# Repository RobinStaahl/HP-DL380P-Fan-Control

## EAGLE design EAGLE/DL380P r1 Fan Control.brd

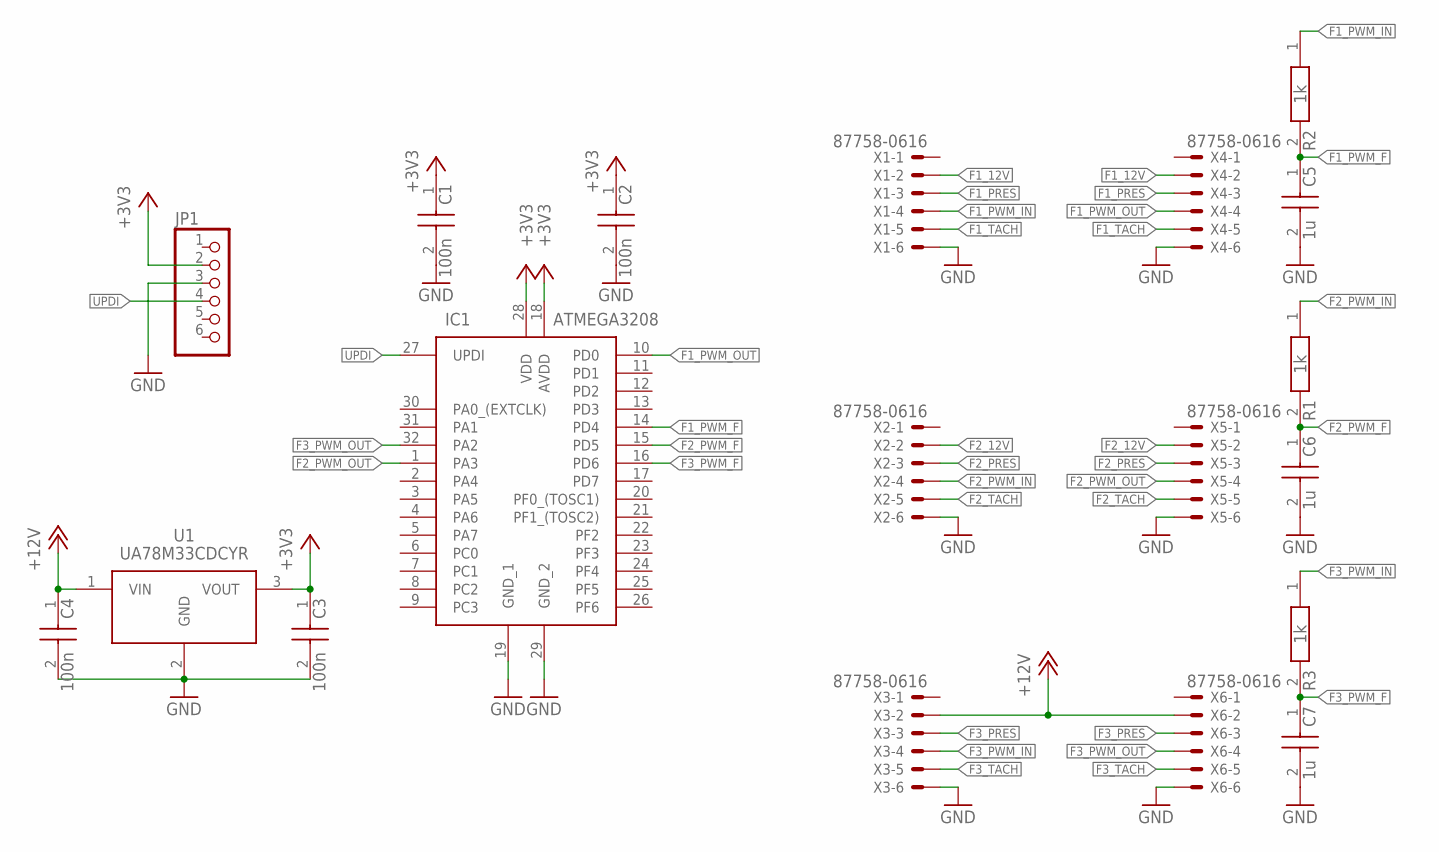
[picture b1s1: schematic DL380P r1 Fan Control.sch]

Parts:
C1, C2, C3, C4: 100n; CAPC1608X90N
C5, C6, C7: 1u; CAPC1608X90N
IC1: ATMEGA3208; QFP80P900X900X120-32N
JP1: PINHD-1X6LOCK; 1X06-BIGLOCK
R1, R2, R3: 1k; RESC1608X55N
U1: UA78M33CDCYR; SOT230P700X180-4N
X1, X2, X3, X4, X5, X6: 87758-0616

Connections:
+3V3: C1.1, C2.1, C3.1, IC1.18 (AVDD), IC1.28 (VDD), JP1.2, U1.3 (VOUT)
+12V: C4.1, U1.1 (VIN), X3.2, X6.2
F1_12V: X1.2, X4.2
F1_PRES: X1.3, X4.3
F1_PWM_F: C5.1, IC1.14 (PD4), R2.2
F1_PWM_IN: R2.1, X1.4
F1_PWM_OUT: IC1.10 (PD0), X4.4
F1_TACH: X1.5, X4.5
F2_12V: X2.2, X5.2
F2_PRES: X2.3, X5.3
F2_PWM_F: C6.1, IC1.15 (PD5), R1.2
F2_PWM_IN: R1.1, X2.4
F2_PWM_OUT: IC1.1 (PA3), X5.4
F2_TACH: X2.5, X5.5
F3_PRES: X3.3, X6.3
F3_PWM_F: C7.1, IC1.16 (PD6), R3.2
F3_PWM_IN: R3.1, X3.4
F3_PWM_OUT: IC1.32 (PA2), X6.4
F3_TACH: X3.5, X6.5
GND: C1.2, C2.2, C3.2, C4.2, C5.2, C6.2, C7.2, IC1.19 (GND_1), IC1.29 (GND_2), JP1.3, U1.2 (GND), U1.4 (GND_1), X1.6, X2.6, X3.6, X4.6, X5.6, X6.6
UPDI: IC1.27 (UPDI), JP1.4

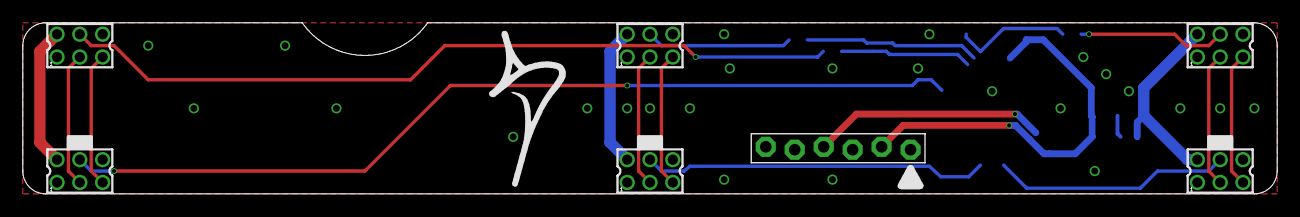
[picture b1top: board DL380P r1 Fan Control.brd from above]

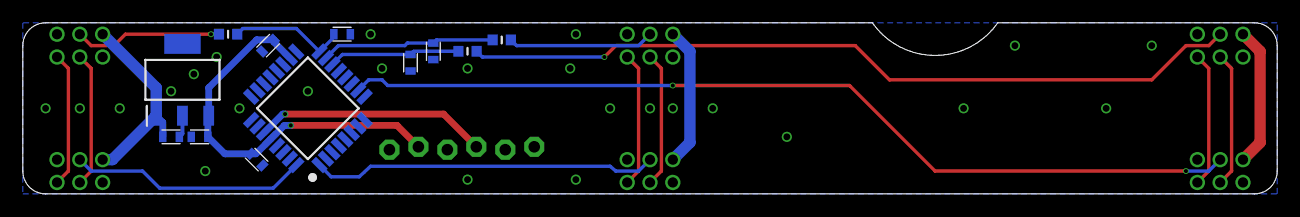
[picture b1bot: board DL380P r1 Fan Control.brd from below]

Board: 2 copper layers, 110.0 x 15.0 mm, 19 parts (12 on the bottom side), 21 nets.

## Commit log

2023-07-19 Init
